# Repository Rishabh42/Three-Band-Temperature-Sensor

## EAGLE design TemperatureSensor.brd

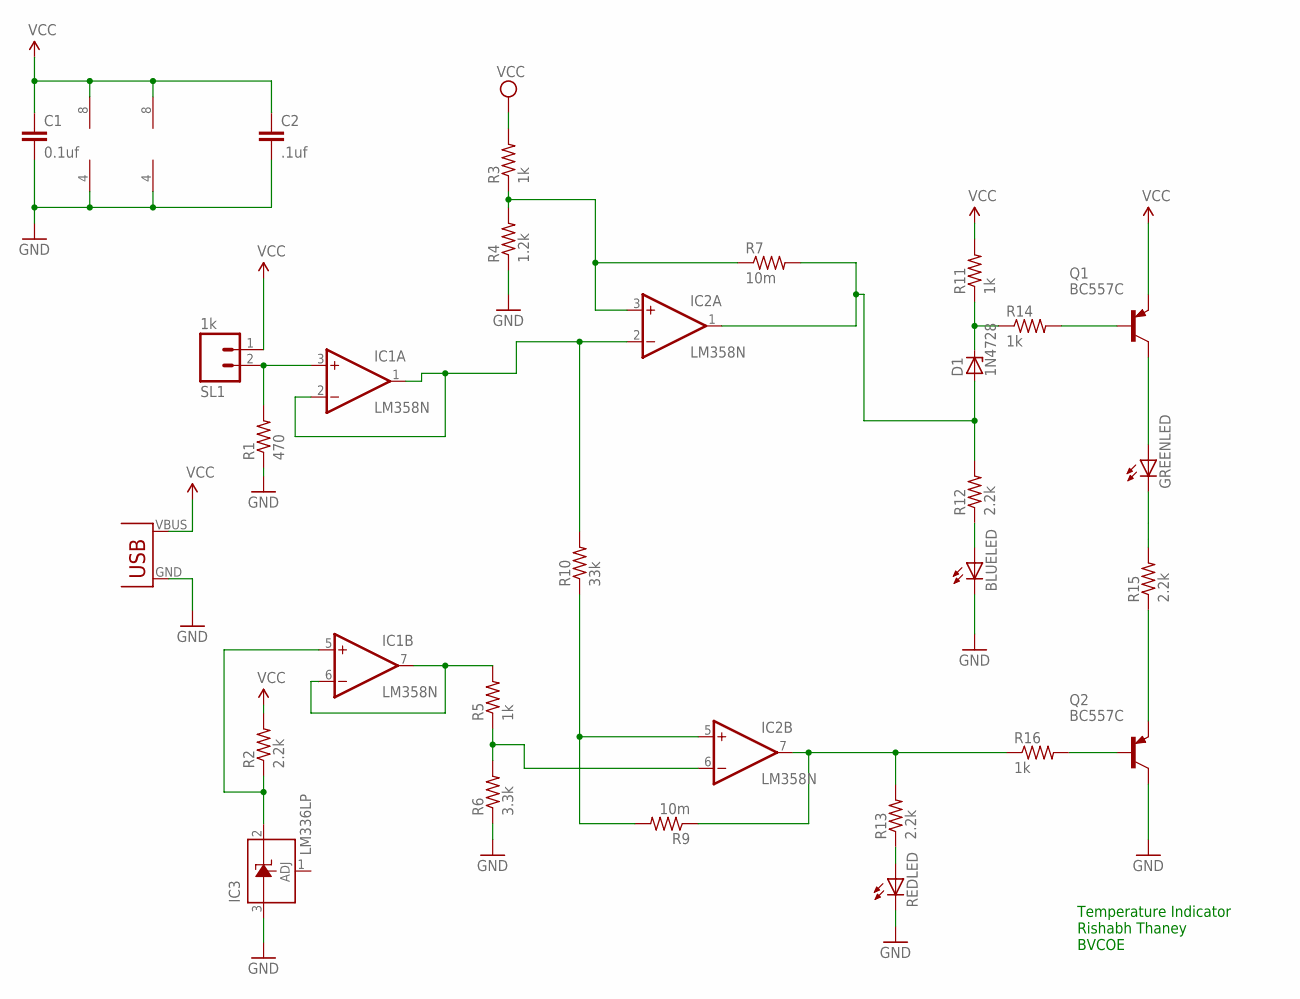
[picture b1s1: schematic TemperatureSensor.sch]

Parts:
BLUELED: LED5MM
C1: 0.1uf; C025-024X044
C2: .1uf; C025-024X044
D1: 1N4728; DO41Z10
GREENLED: LED5MM
IC1, IC2: LM358N; DIL08
IC3: LM336LP; TO92
Q1, Q2: BC557C; TO92-EBC
R1: 470; 0204/7
R2, R12, R13, R15: 2.2k; 0204/7
R3, R5, R11, R14, R16: 1k; 0204/7
R4: 1.2k; 0204/7
R6: 3.3k; 0204/7
R7, R9: 10m; 0204/7
R10: 33k; 0204/7
REDLED: LED5MM
SL1: 1k; 02P
U$1: USB(POWER)

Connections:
GND: BLUELED.K (C), C1.2, C2.2, IC1.4 (V-), IC2.4 (V-), IC3.3 (A), Q2.C, R1.1, R4.1, R6.1, REDLED.K (C), U$1.GND
unnamed: IC1.3 (+IN), R1.2, SL1.2
unnamed: R13.1, REDLED.A
unnamed: IC2.3 (+IN), R3.1, R4.2, R7.1
unnamed: BLUELED.A, R12.1
unnamed: D1.C, R11.1, R14.1
unnamed: D1.A, IC2.1 (OUT), R7.2, R12.2
unnamed: Q1.B, R14.2
unnamed: GREENLED.A, Q1.C
unnamed: GREENLED.K (C), R15.2
unnamed: Q2.E, R15.1
unnamed: Q2.B, R16.2
unnamed: IC2.7 (OUT), R9.1, R13.2, R16.1
unnamed: IC1.6 (-IN), IC1.7 (OUT), R5.2
unnamed: IC2.6 (-IN), R5.1, R6.2
unnamed: IC1.5 (+IN), IC3.2 (C), R2.1
unnamed: IC1.1 (OUT), IC1.2 (-IN), IC2.2 (-IN), R10.2
unnamed: IC2.5 (+IN), R9.2, R10.1
VCC: C1.1, C2.1, IC1.8 (V+), IC2.8 (V+), Q1.E, R2.2, R3.2, R11.2, SL1.1, U$1.VBUS (VCC)

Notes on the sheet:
Temperature Indicator Rishabh Thaney BVCOE

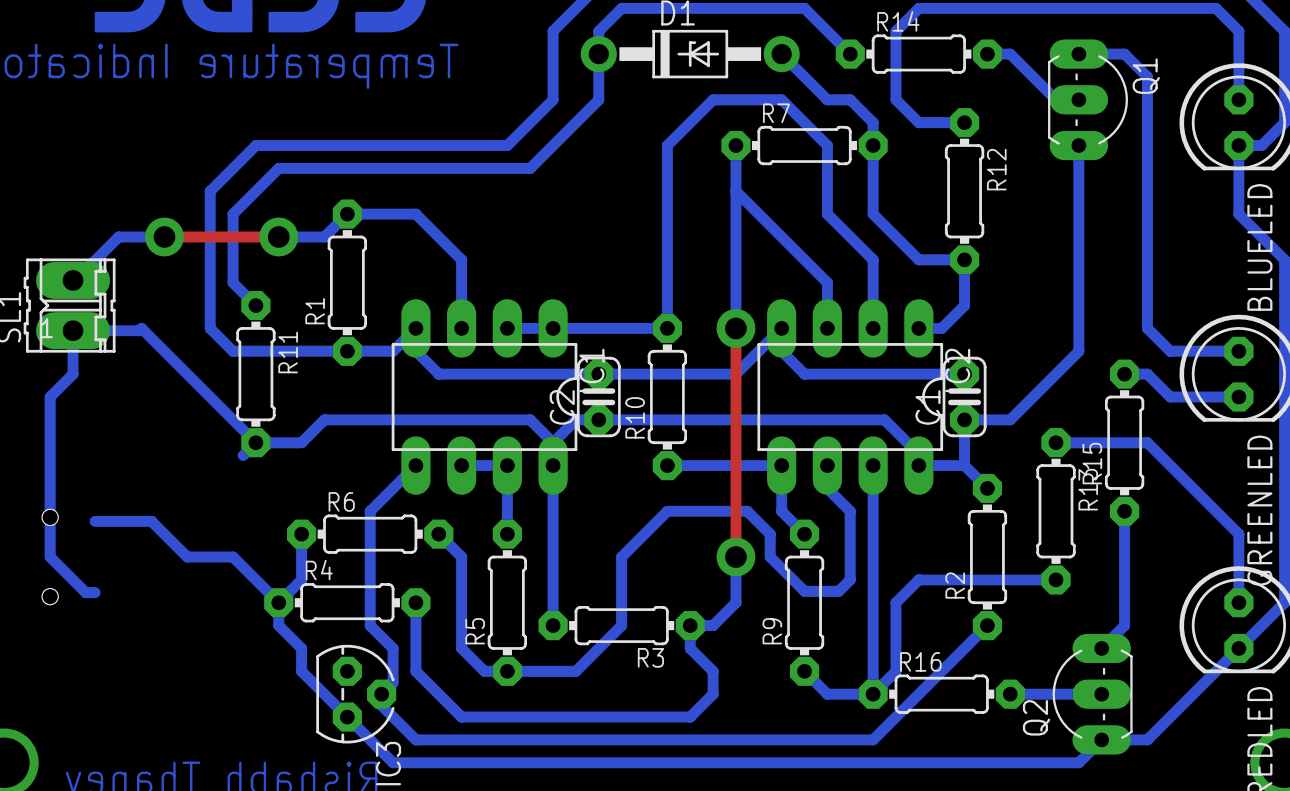
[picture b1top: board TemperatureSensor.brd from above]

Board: 2 copper layers, 29 parts (1 on the bottom side), 19 nets.

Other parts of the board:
U$2: LOGO-CEDT-BOT-18MM
